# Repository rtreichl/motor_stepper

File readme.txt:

Project to drive an step motor.

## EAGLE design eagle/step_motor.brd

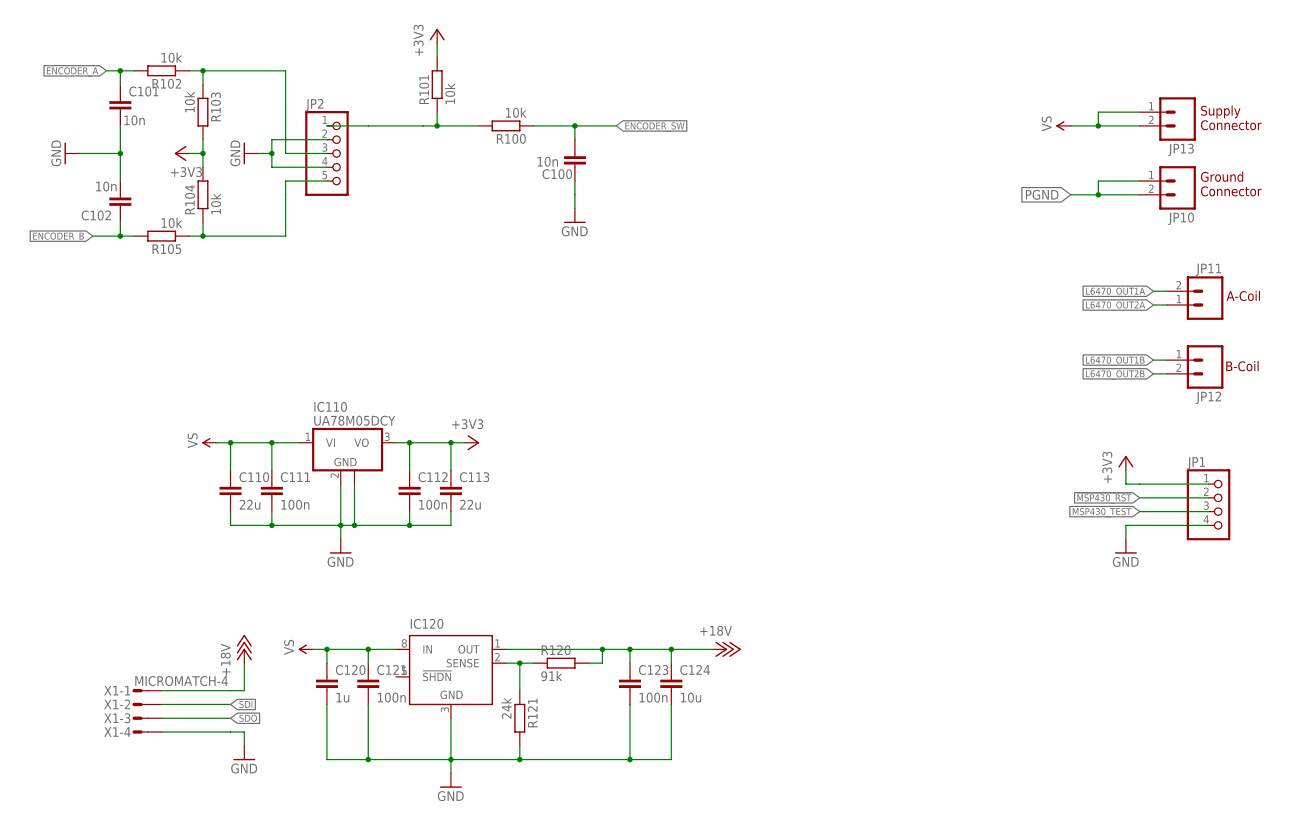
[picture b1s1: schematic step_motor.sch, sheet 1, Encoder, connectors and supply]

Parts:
C100, C101, C102: 10n; C0603
C110, C113: 22u; C1206
C111, C112, C121, C123: 100n; C0603
C120: 1u; C1206
C124: 10u; C1206
IC110: UA78M05DCY; SOT223
IC120: LT1129CS8; SOIC8
JP1: PINHD-1X4; 1X04
JP2: PINHD-1X5; 1X05
JP10, JP11, JP12, JP13: M023.5MM; SCREWTERMINAL-3.5MM-2
R100, R101, R102, R103, R104, R105: 10k; R0603
R120: 91k; R0603
R121: 24k; R0603
X1: MICROMATCH-4

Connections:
!MSP430_RST: JP1.2; also elsewhere on the board
+3V3: C112.1, C113.1, IC110.3 (VO), JP1.1, R101.2, R103.2, R104.2; also elsewhere on the board
+18V: C123.1, C124.1, IC120.1 (OUT), R120.2, X1.1
ENCODER_A: C101.1, R102.2; also elsewhere on the board
ENCODER_B: C102.1, R105.2; also elsewhere on the board
ENCODER_SW: C100.2, R100.1; also elsewhere on the board
GND: C100.1, C101.2, C102.2, C110.2, C111.2, C112.2, C113.2, C120.2, C121.2, C123.2, C124.2, IC110.2 (GND), IC110.4 (GND), IC120.3 (GND), IC120.6 (GND), IC120.7 (GND), JP1.4, JP2.2, JP2.4, R121.2, X1.4; also elsewhere on the board
L6470_OUT1A: JP11.2; also elsewhere on the board
L6470_OUT1B: JP12.1; also elsewhere on the board
L6470_OUT2A: JP11.1; also elsewhere on the board
L6470_OUT2B: JP12.2; also elsewhere on the board
MSP430_TEST: JP1.3; also elsewhere on the board
unnamed: IC120.2 (SENSE), R120.1, R121.1
unnamed: JP2.3, R102.1, R103.1
unnamed: JP2.1, R100.2, R101.1
PGND: JP10.1, JP10.2; also elsewhere on the board
R904: JP2.5, R104.1, R105.1
SDI: X1.2; also elsewhere on the board
SDO: X1.3; also elsewhere on the board
VS: C110.1, C111.1, C120.1, C121.1, IC110.1 (VI), IC120.8 (IN), JP13.1, JP13.2; also elsewhere on the board

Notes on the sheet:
B-Coil
A-Coil
Supply Connector
Ground Connector

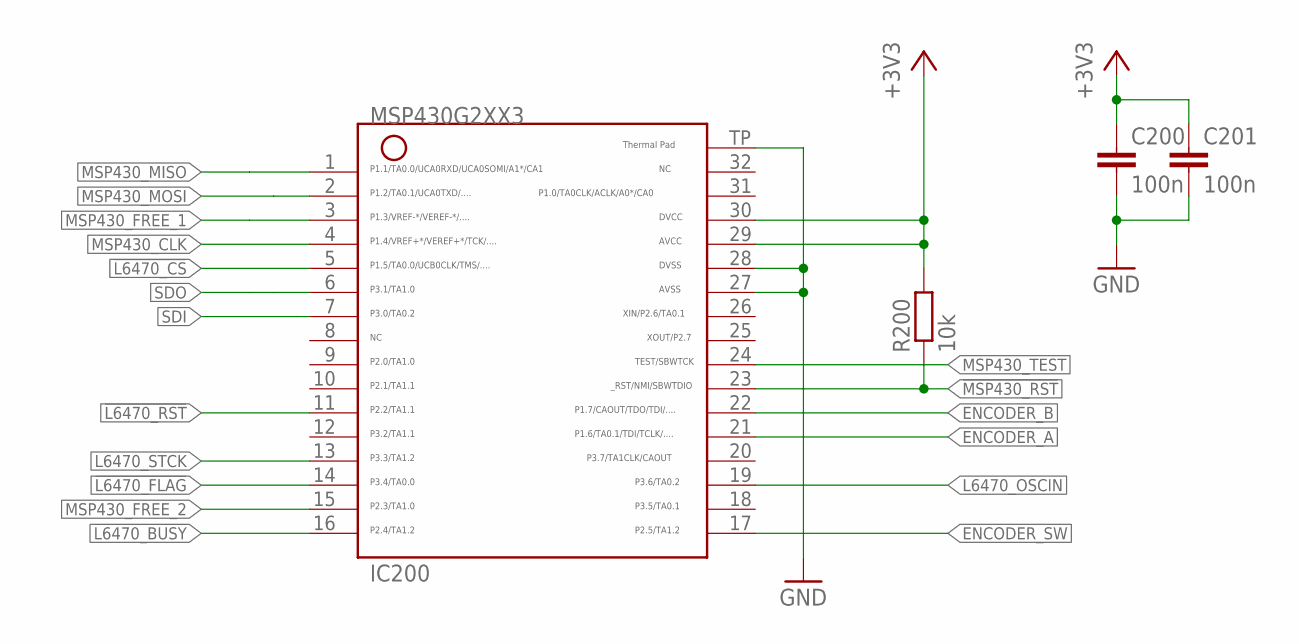
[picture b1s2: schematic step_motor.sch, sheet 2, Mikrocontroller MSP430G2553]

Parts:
C200, C201: 100n; C0603
IC200: G2XX3---RHB32; RHB32
R200: 10k; R0603

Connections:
!L6470_BUSY: IC200.16; also elsewhere on the board
!L6470_CS: IC200.5; also elsewhere on the board
!L6470_FLAG: IC200.14; also elsewhere on the board
!L6470_RST: IC200.11; also elsewhere on the board
!MSP430_RST: IC200.23, R200.1; also elsewhere on the board
+3V3: C200.1, C201.1, IC200.29, IC200.30, R200.2; also elsewhere on the board
ENCODER_A: IC200.21; also elsewhere on the board
ENCODER_B: IC200.22; also elsewhere on the board
ENCODER_SW: IC200.17; also elsewhere on the board
GND: C200.2, C201.2, IC200.27, IC200.28, IC200.TP; also elsewhere on the board
L6470_OSCIN: IC200.19; also elsewhere on the board
L6470_STCK: IC200.13; also elsewhere on the board
MSP430_CLK: IC200.4; also elsewhere on the board
MSP430_FREE_1: IC200.3
MSP430_FREE_2: IC200.15
MSP430_MISO: IC200.1; also elsewhere on the board
MSP430_MOSI: IC200.2; also elsewhere on the board
MSP430_TEST: IC200.24; also elsewhere on the board
SDI: IC200.7; also elsewhere on the board
SDO: IC200.6; also elsewhere on the board

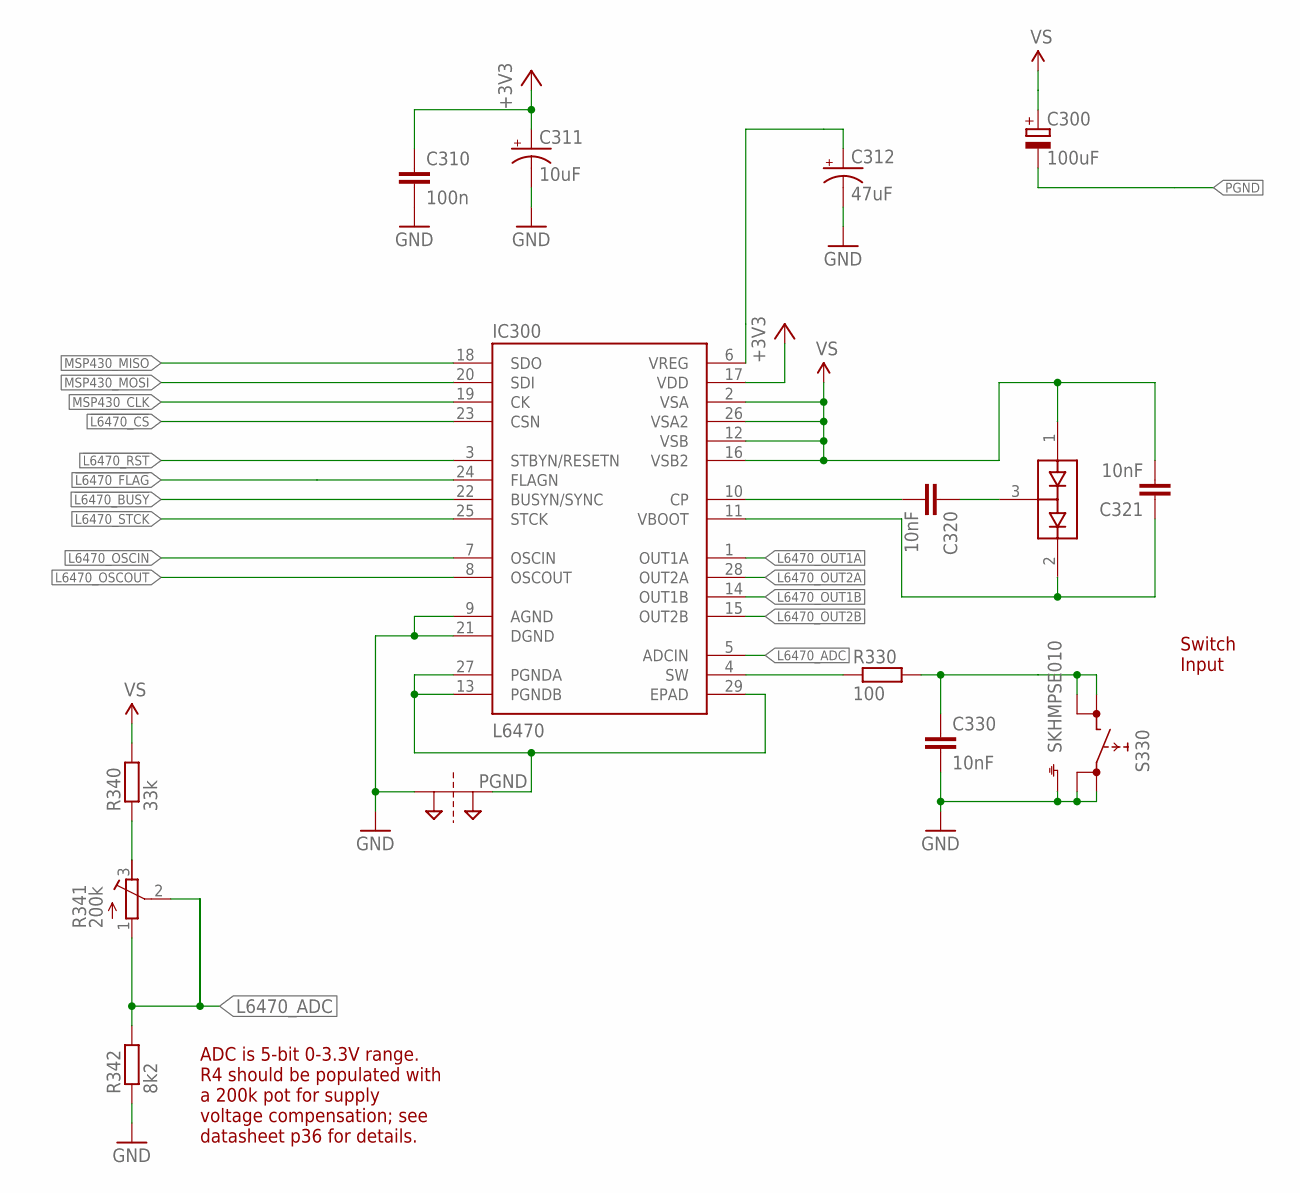
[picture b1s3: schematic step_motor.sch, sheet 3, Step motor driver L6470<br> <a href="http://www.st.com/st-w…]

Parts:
C300: 100uF; PANASONIC_D
C310: 100n; C0603
C311: 10uF; EIA3216
C312: 47uF; EIA3528
C320, C321, C330: 10nF; C0603
D320: BAV99; SOT23
IC300: L6470; HTSSOP28
R330: 100; R0603
R340: 33k; R0603
R341: 200k; RTRIM3224X
R342: 8k2; R0603
S330: SKHMPSE010; SKHMPXE010
SJ2: 2PT_GND_TIE

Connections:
!L6470_BUSY: IC300.22 (BUSYN/SYNC); also elsewhere on the board
!L6470_CS: IC300.23 (CSN); also elsewhere on the board
!L6470_FLAG: IC300.24 (FLAGN); also elsewhere on the board
!L6470_RST: IC300.3 (STBYN/RESETN); also elsewhere on the board
+3V3: C310.1, C311.A (+), IC300.17 (VDD); also elsewhere on the board
C320: C320.2, IC300.10 (CP)
GND: C310.2, C311.C (-), C312.C (-), C330.2, IC300.9 (AGND), IC300.21 (DGND), R342.1, S330.1 (1.1), S330.2 (1.2), S330.5 (SH), SJ2.P$1; also elsewhere on the board
L6470_ADC: IC300.5 (ADCIN), R341.1 (A), R341.2 (S), R342.2
L6470_OSCIN: IC300.7 (OSCIN); also elsewhere on the board
L6470_OSCOUT: IC300.8 (OSCOUT)
L6470_OUT1A: IC300.1 (OUT1A); also elsewhere on the board
L6470_OUT1B: IC300.14 (OUT1B); also elsewhere on the board
L6470_OUT2A: IC300.28 (OUT2A); also elsewhere on the board
L6470_OUT2B: IC300.15 (OUT2B); also elsewhere on the board
L6470_STCK: IC300.25 (STCK); also elsewhere on the board
MSP430_CLK: IC300.19 (CK); also elsewhere on the board
MSP430_MISO: IC300.18 (SDO); also elsewhere on the board
MSP430_MOSI: IC300.20 (SDI); also elsewhere on the board
unnamed: C312.A (+), IC300.6 (VREG)
unnamed: IC300.4 (SW), R330.1
unnamed: C330.1, R330.2, S330.3 (2.1), S330.4 (2.2)
unnamed: C320.1, D320.3 (COM)
unnamed: C321.1, D320.2 (C2), IC300.11 (VBOOT)
unnamed: R340.1, R341.3 (E)
PGND: C300.-, IC300.13 (PGNDB), IC300.27 (PGNDA), IC300.29 (EPAD), SJ2.P$2; also elsewhere on the board
VS: C300.+, C321.2, D320.1 (A1), IC300.2 (VSA), IC300.12 (VSB), IC300.16 (VSB2), IC300.26 (VSA2), R340.2; also elsewhere on the board

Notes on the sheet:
Switch Input
ADC is 5-bit 0-3.3V range. R4 should be populated with a 200k pot for supply voltage compensation; see datasheet p36 for details.

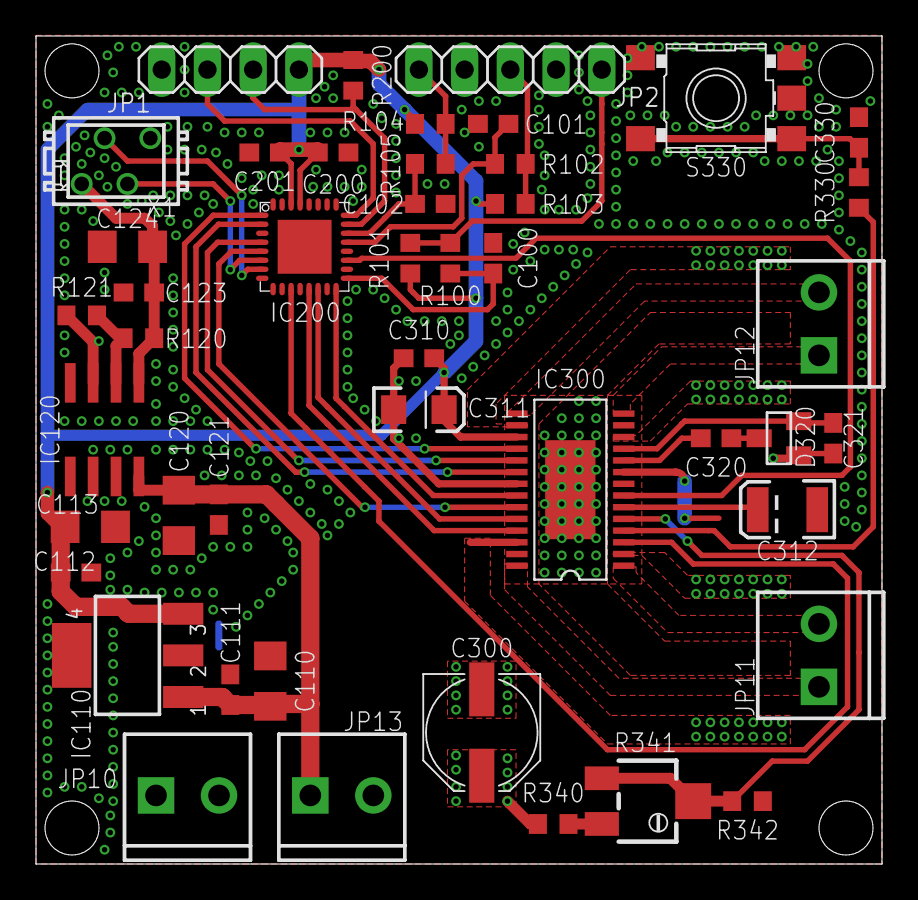
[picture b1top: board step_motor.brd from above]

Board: 2 copper layers, 47.0 x 46.0 mm, 47 parts (1 on the bottom side), 37 nets.

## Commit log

2015-08-13 Init: First schematics to initial project
2016-01-28 CHG: Final board version

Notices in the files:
parts and their libraries:
SparkFun-PowerIC: Licensing: CC v3.0 Share-Alike You are welcome to use this library for commercial purposes.
